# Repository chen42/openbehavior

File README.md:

# OpenBehavior

This project aims to establish a computing platform for rodent behavior research using the Raspberry Pi computer. We are building devices for conducting operant conditioning, as well as some infrared sensor based assays. We also designed an environmental sensor set that records the temperature, humidity, air pressure, ambient light, noise level, etc. 

These projects are in various stages of development. The following are the most mature projects.

## Operant Licking
This project develops a home cage device for operant licking (fixed ratio, various ratio, or progressive ratio schedules). Detailed description of this project is published in a [PeerJ article]( https://peerj.com/articles/2981/) 

## EnvSensors

This device collects four environmental variables and we have several of them running in the lab. This device is also described in our [PeerJ article](https://peerj.com/articles/2981/)

## RFID 

This project develops a standalone RFID reader for the EM4100 implantable glass chips. We use this daily in the lab.

## Extinction

This device is used to run extinction experiments as described  by [Wang et al. (2014)](www.ncbi.nlm.nih.gov/PubMed/25532105) 

## Motion

This project adds a motion sensor to standard operant chambers.

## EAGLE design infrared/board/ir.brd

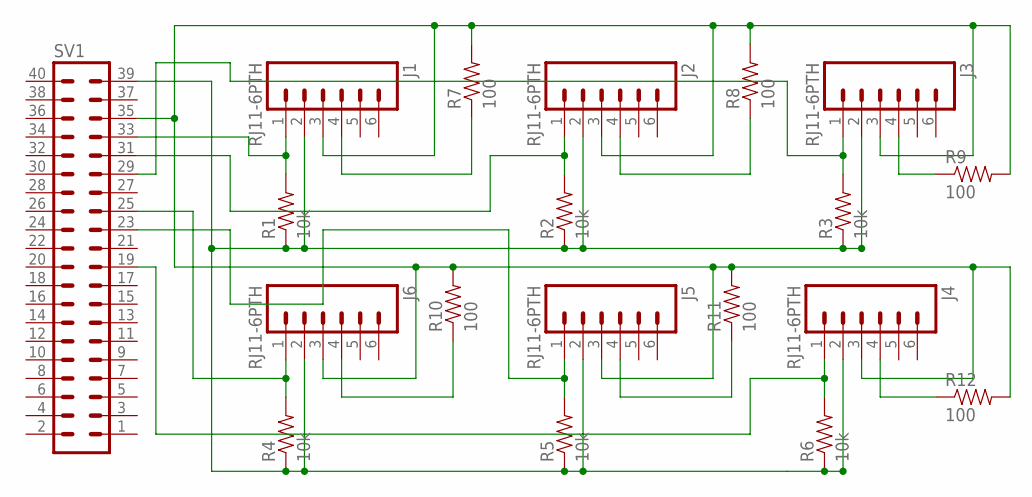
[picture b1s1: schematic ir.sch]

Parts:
J1, J2, J3, J4, J5, J6: RJ11-6PTH; RJ11-6
R1, R2, R3, R4, R5, R6: 10k; AXIAL-0.3
R7, R8, R9, R10, R11, R12: 100; AXIAL-0.3
SV1: MA20-2

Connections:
unnamed: J1.2, J2.2, J3.2, J4.2, J5.2, J6.2, R1.P$1 (1), R2.P$1 (1), R3.P$1 (1), R4.P$1 (1), R5.P$1 (1), R6.P$1 (1), SV1.39
unnamed: J2.1, R2.P$2 (2), SV1.31
unnamed: J3.1, R3.P$2 (2), SV1.29
unnamed: J6.1, R4.P$2 (2), SV1.25
unnamed: J5.1, R5.P$2 (2), SV1.23
unnamed: J4.1, R6.P$2 (2), SV1.19
unnamed: J1.1, R1.P$2 (2), SV1.33
unnamed: J1.3, J2.3, J3.3, J4.3, J5.3, J6.3, R7.P$2 (2), R8.P$2 (2), R9.P$2 (2), R10.P$2 (2), R11.P$2 (2), R12.P$2 (2), SV1.35
unnamed: J1.4, R7.P$1 (1)
unnamed: J2.4, R8.P$1 (1)
unnamed: J3.4, R9.P$1 (1)
unnamed: J6.4, R10.P$1 (1)
unnamed: J5.4, R11.P$1 (1)
unnamed: J4.4, R12.P$1 (1)

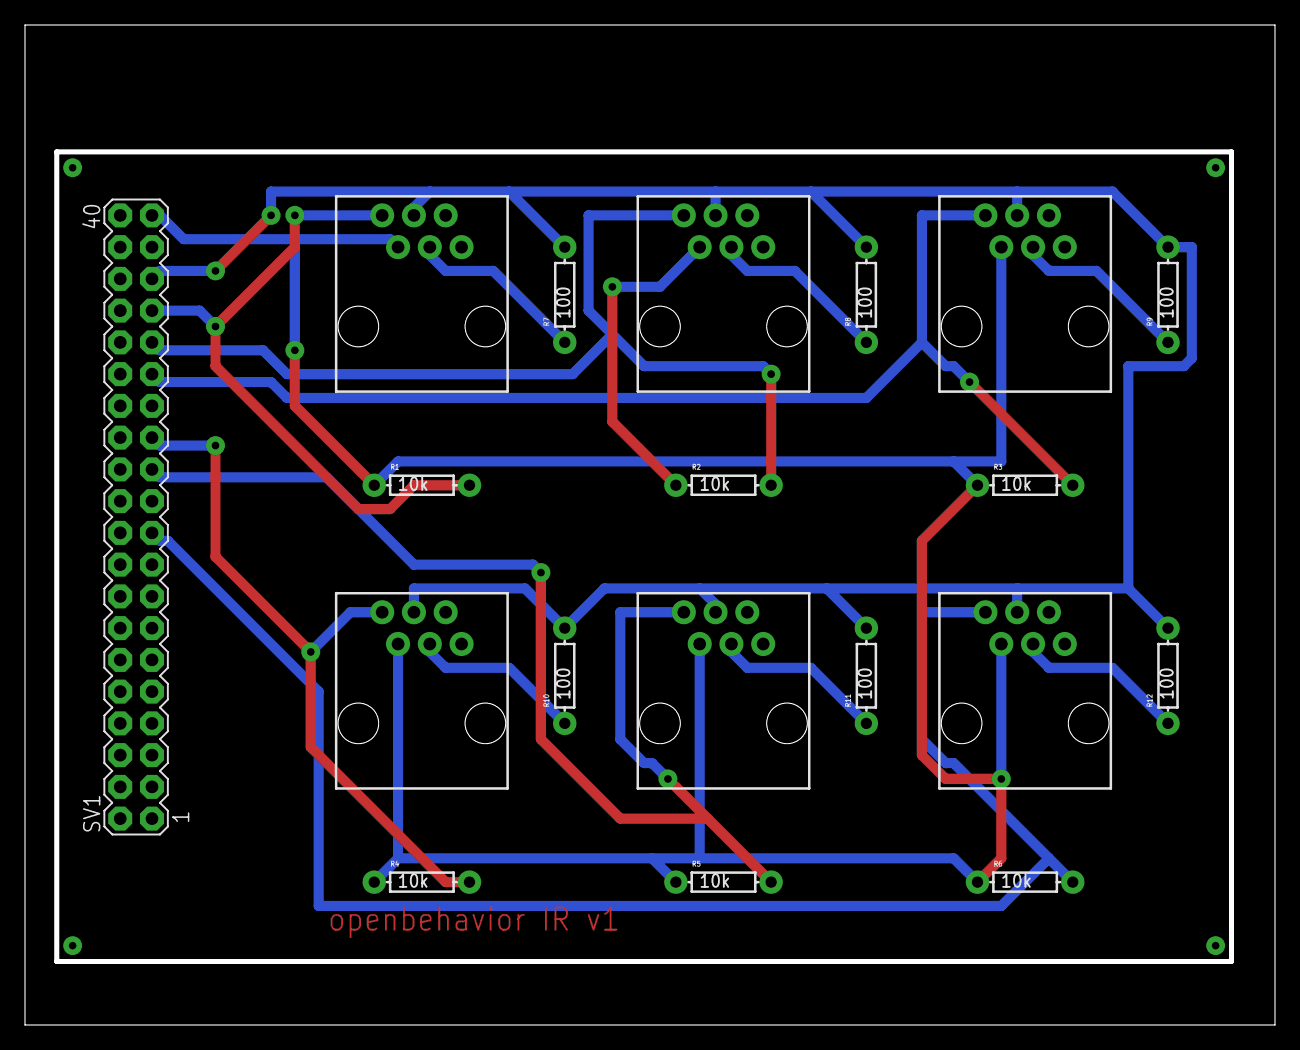
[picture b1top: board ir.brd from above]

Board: 2 copper layers, 99.6 x 79.6 mm, 19 parts (0 on the bottom side), 14 nets.

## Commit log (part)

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2016-07-14 use the last 8 char of the RFID
2016-07-14 case and cover
2016-07-14 minor adjustment of lcd position
2016-07-14 add powercord to the pi
2016-07-15 Extinction box wiring documentation
2016-07-15 add LED box designed by Cindy
2016-07-15 update LCD every 60 sec
2016-07-15 reduce touch sensor sensitivity
2016-07-17 add session id to extinction test
2016-07-17 set htpdate timeout
2016-07-17 adjust time resolution for licking response
2016-07-19 add slots for viewing the LED on the Pi
2016-07-20 update network policy
2016-07-20 add slant to spout holder
2016-07-24 add LCD, use gpio.BCM
2016-07-24 add openning for LCD panel
2016-07-24 a bar to close the RFID antenna
2016-07-25 adjust RFID hook size
2016-07-25 minor adj position of the Pi
2016-07-25 minor adjust of mounting position
2016-07-28 enlarged the hook for RFID antenna
2016-07-28 update doc for the RPi/LCD pin connections
2016-07-28 variable ratio 10
2016-08-01 modify RFID antenna holder
2016-08-02 update LCD messages
2016-08-02 change LCD message
2016-08-03 update hwclock script
2016-08-03 add RIFD scan lapse
2016-08-03 adjust lcd refresh time
2016-08-03 matrix to cut rat brains
2016-08-04 fix bugs: motion session ID was 1 higher; ratID was from prev.; change file name conv.
2016-08-12 add mounting screw to the motor mount
2016-08-12 minor adj of sizes
2016-08-12 add rsync to end end of the run
2016-08-12 readj size of the bearings
2016-08-15 update rtc mounting screw position for both rtc models
2016-08-17 fix rubber band hooks sticking out
2016-08-19 Thanks @longlius
2016-08-21 change dir names
2016-08-21 small increade in gudie rod diameter for easier insertion
2016-08-22 remove old c code
2016-08-22 PR ratio
2016-08-23 fix bug in vr initial ratio
2016-08-23 remove session length. session controlled by the offpin. add session ID
2016-08-23 show the loaded prog.
2016-08-24 data file use nextratio instead of ratio
2016-08-24 record schedule in data file. clean code
2016-08-24 update display messag
2016-08-25 simply data format
2016-08-25 fix motion recording length for PP and other PR bugs
2016-08-26 adjust nut size for syringe hook
2016-08-29 adjust pump motor mount screw location
2016-08-29 modify rod size
2016-08-29 nut width
2016-08-30 hwclock
2016-09-05 update rat Button
2016-09-05 extinction files updated
2016-09-05 update extinction
2016-09-05 update stl files for brain slicer
2016-09-06 update RFID reader readme
2016-09-06 RFID reader readme.md
2016-09-06 update readme files
2016-09-07 parts list
2016-09-07 add cover stl
2016-09-08 env sensor frame draft
2016-09-08 stage the reading by 5 s
2016-09-09 envSensor images
2016-09-09 assembly instruction
2016-09-09 cleanup a bit more
2016-09-09 edit the readme
2016-09-09 Fixed spelling mistake in preamble.
2016-09-09 Wrong tense of the verb 'to run'
2016-09-09 Misc fixes so things make sense.
2016-09-09 adjust diameter for stainless steel guide rod
2016-09-11 parts list as its own file
2016-09-11 tweaking the md files
2016-09-11 crop some images
2016-09-13 fix image file name
2016-09-13 add link to preprint
2016-09-13 update dirname
2016-09-13 update dim
2016-09-15 add video link
2016-09-15 add assembled images
2016-09-15 fix typo
2016-09-16 add images
2016-09-16 cleaned up Assembly.md
2016-09-16 spot light on projects
2016-09-16 abstracted serial device name to constant
2016-09-16 started separate RFID scanner module for handling RFID stuff
2016-09-27 add image
2016-09-27 correct url for preprint
2016-09-30 added method to figure out raspberry pi version
2016-10-19 add a third touch pin for waterwq
2016-10-25 make it larger
2016-10-27 added code to dynamically detect raspi version and choose correct serial line
2016-11-03 starting simplying pump frame to reduce friction
2016-11-03 modified the motor end
2016-11-04 adjust sizes of end_motor components
2016-11-08 finalized motor_end
2016-11-10 add a different tail cover
2016-11-11 Script to handle raspberry pi 3
2016-11-15 further loosen syringe carrier to reduce friction
2016-11-15 adjust syringe carrier size after printing
2016-11-16 add a second nut trap for syringe carrier
2016-11-19 skip hwclock on ExtBoxes
2016-11-19 trying to shut down wlan0
2016-11-19 making sure wlan0 is turned off before extinction session starts
2016-11-20 clean up pump design
2016-12-05 completing the bluetooth disabling script
2016-12-06 disable hciuart according to @longlius
2016-12-14 update images
2016-12-14 update assembly instruction
2016-12-14 update assembly instructions
2016-12-16 add images, update assembly and partslist
2017-03-16 fix broken links
2017-03-16 update PeerJ
2017-03-16 update links
2017-03-18 change fr to FR2TO2
2017-03-31 fr5to5
2017-04-04 increase pitch to 1.0, reduce high pitch noise
2017-04-11 try FR10
2017-04-24 add timeout to the data file, change to FR2TO2
2017-04-28 timeout =5
2017-04-28 Added serial port and cylon.js
2017-04-28 Added a script to start a rabbitmq service in a docker container with default values.
    Added documentation in rabbitmq middleware start script on how to configure environment variables.
    Added a script to stop the rabbitmq service
2017-04-28 Added a JSON file for configuring the OpenBehavior system.
2017-04-28 Added a new base class for interacting with RabbitMQ
2017-04-28 Added base classes for a generic Sensor. As well added files for implementing concrete sensor devices in OpenBehavior
2017-04-28 Added a generic logger interface. Also added a file for implementing a concrete data logger virtual device
2017-04-28 Added npm init, with npm setup
2017-04-28 Started work on Schemas for openbehavior configuration files.
2017-04-28 Added npm package for writing schemas.
2017-04-28 Updated Config Schemas with a fleshed out schema for Schedule objects.
2017-04-28 Updated OpenBehavior config with all Schedules, PR, FR, VR, EXT
2017-05-12 try fr2to10
2017-06-21 add a hole to the bottom of the spout holder
2017-07-10 enlarge nose cone hole
2017-07-10 plastic plates are not conductive
2017-08-02 add rat ear tag
2017-08-09 novel object for rats
2017-08-09 hollow it out
2017-08-11 rpi camera mount for record video of rats
2017-08-11 enlarge the center hole
2017-09-12 count only licks within clusters
2017-09-12 act and ina only record licks within a cluster
2017-09-15 fix counter > next ratio bug
2017-10-19 change extinction
2017-12-12 start 22h
2017-12-12 rfid correction
2018-01-24 visual cue reinstatement
2018-01-25 define vreinstate
2018-07-26 add del trial
2018-07-28 correct date time if necessary, copy data when done
2018-08-01 remove buzzer, calibrate time
2018-08-13 rename
2018-10-09 case for the antenna
2018-10-09 shorter for better fit
2018-10-11 manually enter RFID
2019-04-30 retain up to five lines
2019-04-30 case with no lid
2019-04-30 clarify readme.
2019-05-01 case update
2019-05-01 last 4 char
2019-05-01 cover
2019-05-02 adjust epaper location
2019-07-14 testing a new motor controller
2019-08-09 stronger base
2019-08-19 adjust position of the view port
2019-09-18 rfid board cover
2019-09-18 write rfid and time
2019-09-19 collecting stuff
2019-09-19 re-org data logger
2019-09-19 clean up a bit
2019-09-19 cboard cover screw head
2019-09-22 add lib
2019-09-22 add IDS
2019-09-23 separting operant out as subprocess
2019-09-23 remove unused files
2019-09-23 data format
2019-09-23 everything working for now
2019-09-24 sample timer code with two rats
2019-09-24 reorg data display, add timeout to display
2019-09-24 calibrate pump
2019-09-30 motor housing with heat sink
2019-10-03 no longer broken by rats
2019-10-04 formating
2019-10-05 when info on RFID might be stale
2019-10-05 oval front panel
2019-10-07 can't program in the animal room
2019-10-07 fix unknow
2019-10-08 make the spout deeper
2019-10-08 use USB rfid reader
2019-10-09 start readme.md
2019-10-11 improved dialog
2019-10-11 better questions
2019-10-14 improve user dialog interface
2019-10-15 rfid must be rat specific
2019-10-16 warning messages'
2019-10-18 Added some comments and make modules to print different parts
2019-10-23 Modified the case for tailTimer. About 85% done. Still need to add a side wall and some screws and make sure the radius of the screw fits.
2019-10-25 tailTimer first final commit.
2019-11-13 minor changes
2020-01-20 spring goes inside
2020-01-20 ear tag for rats
2020-01-20 add stl for complete design
2020-03-20 pump move code by Jie
2020-03-20 pump designs openscad code
2020-06-15 modify pump move (button)
2020-09-04 tail timer case
2020-09-07 fix run command
2020-09-08 add pump move
2020-09-15 check if tailtimer directory exist
2020-09-16 udpate run
2020-09-16 operant1 add checking directory
2020-09-22 add schedule to file name
2020-09-22 pump move
2020-09-22 code modification
2020-09-22 add '_' to file name
2020-09-23 check and verify nonidentical rat IDs
2020-09-25 function grouping
2020-09-30 record licks within 1 sec interval only
2020-09-30 discard previous record base on ILI
2020-09-30 fix interval checking logic
2020-10-01 fix rat1 & rat2 ID duplicate comparison
2020-10-02 start pump sooner
2020-10-02 add date to data file name
2020-10-02 lower center hole in front panel
2020-10-04 remove space in file name
2020-10-05 increase maxILI based on pilot data
2020-10-05 change rfid key assignment
2020-10-06 simply output to the screen
2020-10-06 limit pump moving forward
2020-10-06 add micro switch codes to limit the pump move
2020-10-12 forward limit
2020-10-12 push backward button to reset syringe position
2020-10-13 force gzip
2020-10-14 fix library conflict and change data file format when syringe is empty
2020-10-15 use last 8 char for initial RFID
2020-10-15 change RFID data location
2020-10-16 rfid fix
2020-10-16 fix RFID digits
2020-10-16 add keys
2020-10-16 add color print
2020-10-16 add print statement to check RFID
2020-10-17 remove syringe empty message for inactive
2020-10-17 add debug print statement
2020-10-17 key error handling, print debugging statements
2020-10-19 update debugging print statements
2020-10-20 session id increment only on session start
2020-10-20 update sesID
2020-10-20 change subprocess program name
2020-10-21 list unpacking fix
2020-10-21 fix final log bugs
2020-10-21 final log fix
2020-10-21 modify final log file name & record poke count corresponding to each rfid
2020-10-23 modify sync
2020-10-23 log files for active and inactive poke
2020-10-23 file not found handling for final log
2020-10-23 final log logic fix
2020-10-23 remap command RFIDs
2020-10-23 start pump after first command ID is scanned
2020-10-23 fix scan command id logic
2020-10-27 add rat activity counter class to record activity counts
2020-10-27 add pump test
2020-10-27 add active lick counts, when syringe is empty, to final log file
2020-11-03 add error log
2020-11-05 rat#2 ID check fix
2020-11-06 modify get ratid and scantime
2020-11-06 add command ids to the ID config file
2020-11-06 add button logic to PumpMove class (separate from the main)
2020-11-13 change the order of active/inactive pokes in the .tab file
2020-11-13 add session start time to .tab file
2020-11-14 reduce cue light from 5 sec to 0.5 sec
2020-11-16 add 2h rfid
2020-11-17 fix vr ratio
2020-11-17 modify nextratio
2020-11-18 arrange pump move code
2020-11-18 rearrange
2020-11-20 getting session info from class
2020-11-20 main code refactoring
2020-11-20 adjust amount of solution for 20ML syringe
2020-11-23 modify house/cue light logic
2020-11-23 add sudo to run subprocess
2020-11-27 turn off light when the time is not between 9PM and 9AM
2020-12-02 call blinkenlights from operant at exactly 9AM to turn off house light
2020-12-02 scan the same command RFID to start program
2020-12-04 TailTimer - add RFID for ShuangYing
2020-12-04 turn off light after session is over
2020-12-04 use relative path
2020-12-07 add prompt for scanning the rat
2020-12-08 run session without scanning rat id
2020-12-10 disbale flashing light after syringe is empty
2020-12-15 remove poke count temp file after reading
2020-12-16 script for git pull and reboot
2020-12-17 add script to check empty program files at start up
2020-12-17 remove the corrupted project and reclone if any of the program file is not found
2021-01-12 add configuration file containing User and Command RFIDs
2021-04-07 make user test again if the first two test's latency difference is greater than 1 sec
2021-04-20 update tailtimer

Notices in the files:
parts and their libraries:
SparkFun-Connectors: Licensing: Creative Commons ShareAlike 4.0 International - https://creativecommons.org/licenses/by-sa/4.0
